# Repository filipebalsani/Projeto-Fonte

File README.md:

# Projeto-Fonte
O Projeto consiste em criar o circuito de uma fonte de tensão ajustável entre 3V e 12V com apacidade de 100mA usando o simulador [Falstad](https://www.falstad.com/circuit/) e em seguida transformar esse circuito de representação simbólica em um Projeto do Esquemático e PCB (printed circuit board) usando a ferramenta EAGLE.
## Imagem do [Circuito no Falstad](https://tinyurl.com/yhj39fy2)

## [Vídeo](https://drive.google.com/file/d/1WGpKbrKfWXlp82_RFDeCWor8EP2RXax8/view?usp=sharing "Vídeo") Explicando o Circuito
## Valor do Capacitor
Para chegar no valor do capacitor visando um ripple (variação de onda) próximo dos 10% testes foram feitos na simulação do falstad com capacitores de valores diferentes no circuito. A conclusão foi que o valor de 470uF produz uma onda com um pico de 20.267 V e um ponto mínimo de 18.102 V:

E comparando a diferença entre o ponto máximo (20.267 V) e o pointo mínimo (18.102 V) se obtém o ripple da onda que é 10.68 % :

`20.267 V - 18.102 V = 2.165 V = ripple em volts`
`(2.165 V / 20.267 v) * 100 = 10.68 % = ripple em porcentagem `
## Componentes do Circuito
+ #### Fonte de Tensão
Para alimentar o circuito será preciso liga-lo numa tomada de 110v, portanto será usado  no circuito sumilado do falstad uma fonte de tensão de corrente alternada com 2 terminais configurada com uma **Tensão Máxima** de 179.6V e uma **Frequência** de 60Hz.
Tomada                                                                                      | Onda da Tensão da Tomada
:------------------------------------------------------------------------------------------:|:------------------------------------------------------------------------------------------:
|
+ #### Transformador
O primeiro componente do circuito é o transformador que tem como função diminuir a tensão de entrada de 127V para 15V.
Voltagem antes do Transformador                                                             | Voltagem depois do Transformador
:------------------------------------------------------------------------------------------:|:------------------------------------------------------------------------------------------:
|
+ #### Diodo
A próxima parte do circuito é a ponte de diodo que tem como função é retificar a corrente fazendo com que o semiciclo negativo fique positivo. Além disso cada diodo consome 0.7V portanto a ponte gera uma queda de tensão de 1.4V já que somente dois diodos ficam ativos de cada vez.
Voltagem antes da Ponte de Diodo Retificadora                                               | Voltagem depois da Ponte de Diodo Retificadora
:------------------------------------------------------------------------------------------:|:------------------------------------------------------------------------------------------:
|
|A diferença entre o pico antes da ponte de diodo (21.192 V) e depois da ponte de diodo (19.766 V)|é causada por conta da queda de tensão de 0.7V que cada diodo causa (21.192 - 19.766 = 1.426 V)
+ #### Capacitor
O próximo componente é o capacitor que faz a filtragem diminuindo a variação de tensão do circuito chamada de _ripple_ (diferença entre o valor do pico da variação da tensão e o valor do ponto mais baixo da variação da tensão) e deixando a tensão e a corrente mais estáveis.
Voltagem antes do Capacitor                                                                 | Voltagem depois do Capacitor
:------------------------------------------------------------------------------------------:|:------------------------------------------------------------------------------------------:
|

|Os dois gráficos sobrepostos                                                                  |
|:--------------------------------------------------------------------------------------------:|
||
+ #### Resistor
Os resistores limitam a corrente e são usados para proteger componentes que queimariam se uma corrente muito alta passasse por eles devido ao calor que seria gerado.
+ #### LED (light emitting diode)
Serve para indicar que o circuito está ligado. É um diodo que emite uma luz quando uma corrente passa por ele.
+ #### Diodo Zener
O Zener faz a função de regulagem que visa cessar a variação de tensão do circuito. É um dido com uma barreira de tensão mais baixa que deixa a corrente passar assim que receber uma tensão maior que sua barreira, que no zener desse ciruito é 13V.
|Gráfico da corrente e tensão final com o ptênciometro ajustado para 12V                    | 
:------------------------------------------------------------------------------------------:|
|
+ #### Potenciômetro
É um resistor que pode variar o valor de sua resistência permitindo ajustar a tensão do circuito entre 12V e 3V.
|Gráfico da corrente e tensão final com o ptênciometro ajustado para 3V                    | 
:------------------------------------------------------------------------------------------:|
|
+ #### Transistor Bipolar NPN
O transistor permite a passagem de corrente de forma ajustável.
## Circuito no EAGLE

## PCB no EAGLE

## Tabela de Componentes
Componente|Quantidade|Preço
---|---|---
[Transformador 15V](https://proesi.com.br/transformador-entrada-110-220v-saida-7-5-7-5-200ma.html)|1x|R$ 28,95
[Diodo 1N4004](https://proesi.com.br/1n4004-diodo.html)|4x|R$ 0,08
[Capacitor 470uF](https://www.baudaeletronica.com.br/capacitor-eletrolitico-470uf-35v.html)|1x|R$ 0,77
[LED](https://proesi.com.br/led-difuso-5mm-vermelho.html)|1x|R$ 0,21
[Resistor 2.2k](https://proesi.com.br/resistor-carbono-cr25-1-4w-2k2.html)|2x|R$ 0,03
[Resistor 1k](https://proesi.com.br/resistor-carbono-cr25-1-4w-1k.html)|1x|R$ 0,03
[Diodo Zener 13V](https://proesi.com.br/diodo-zener-1-4w-1n964-13v-bzx79c13v.html)|1x|R$ 0,12
[Potenciômetro 5K](https://proesi.com.br/potenciometro-linear-l15-5k-16mm-eixo-estriado.html)|1x|R$ 1,75
[Transistor NPN](https://proesi.com.br/bc337-transistor.html)|1x|R$ 0,23

Valor Total: R$ 32,44

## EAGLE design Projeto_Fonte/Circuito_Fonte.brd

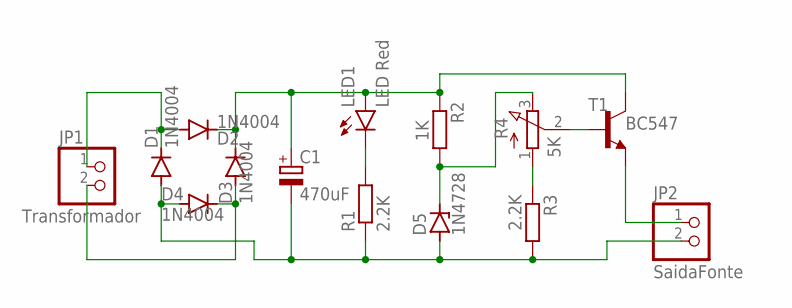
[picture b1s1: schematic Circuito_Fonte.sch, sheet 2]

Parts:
C1: 470uF; E5-10,5
D1, D2, D3, D4: 1N4004; DO41-10
D5: 1N4728; DO41Z10
JP1: Transformador; 1X02
JP2: SaidaFonte; 1X02
LED1: LED Red; LED5MM
R1, R3: 2.2K; 0204/7
R2: 1K; 0204/7
R4: 5K; 3RP/1610N
T1: BC547; TO92

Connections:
unnamed: D1.C, D2.A, JP1.1
unnamed: D3.A, D4.C, JP1.2
unnamed: C1.+, D2.C, D3.C, LED1.A, R2.1, T1.3 (C)
unnamed: LED1.K (C), R1.2
unnamed: D5.C, R2.2, R4.3 (E)
unnamed: R3.1, R4.1 (A)
unnamed: R4.2 (S), T1.2 (B)
unnamed: JP2.1, T1.1 (E)
unnamed: C1.-, D1.A, D4.A, D5.A, JP2.2, R1.1, R3.2

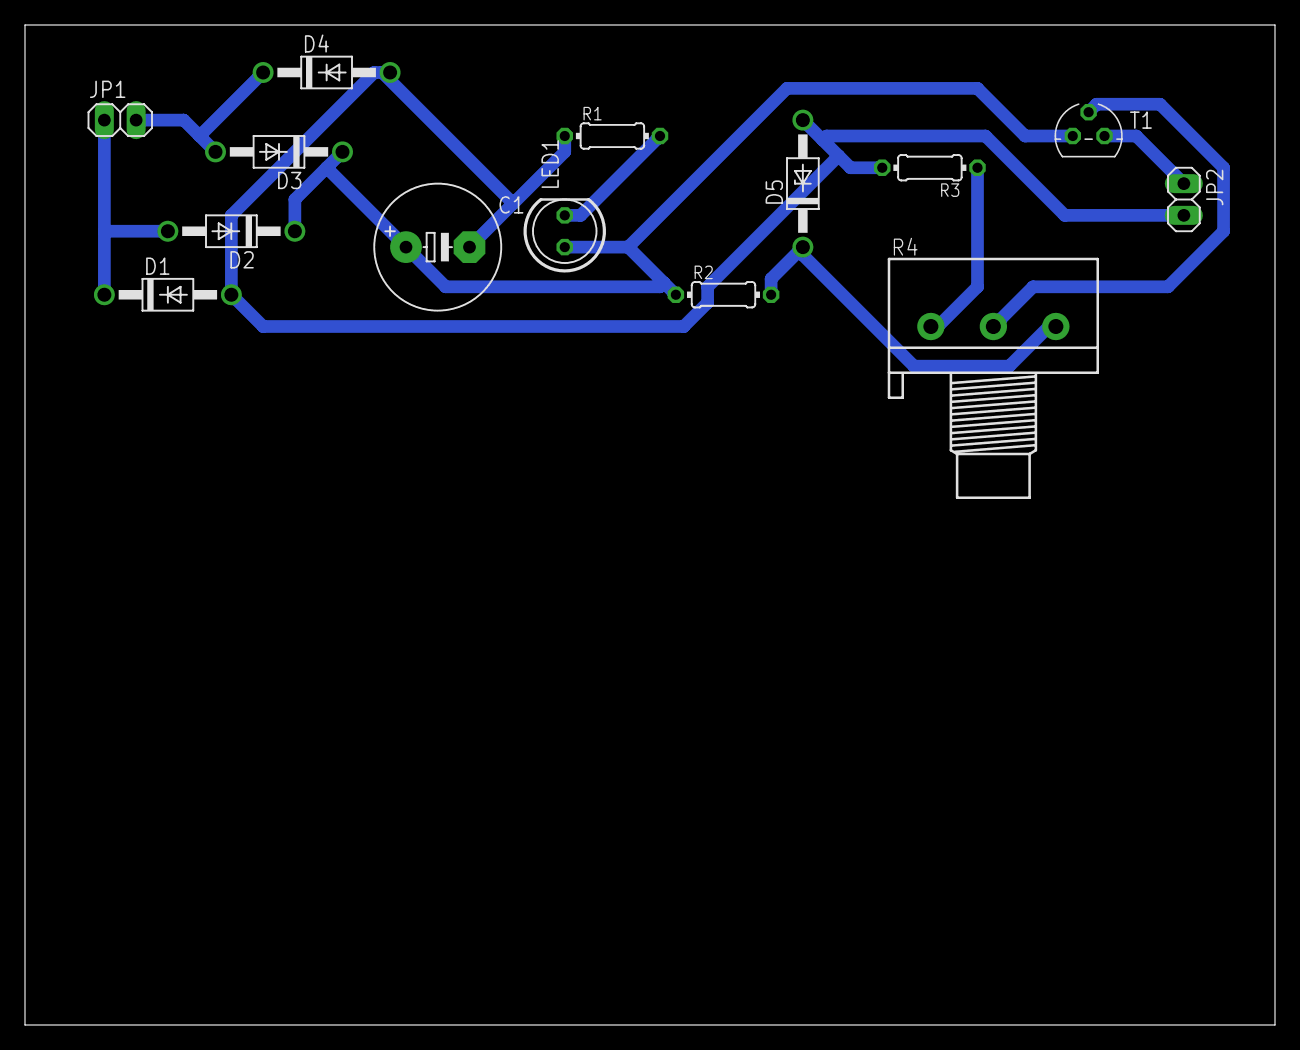
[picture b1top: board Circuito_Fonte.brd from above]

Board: 2 copper layers, 100.0 x 80.0 mm, 14 parts (0 on the bottom side), 9 nets.
